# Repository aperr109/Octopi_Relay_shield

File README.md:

# Octopi_Relay_shield
simple relay shield for controlling a 3D printers power supply via a relay, using an octoprint configured RaspPi device

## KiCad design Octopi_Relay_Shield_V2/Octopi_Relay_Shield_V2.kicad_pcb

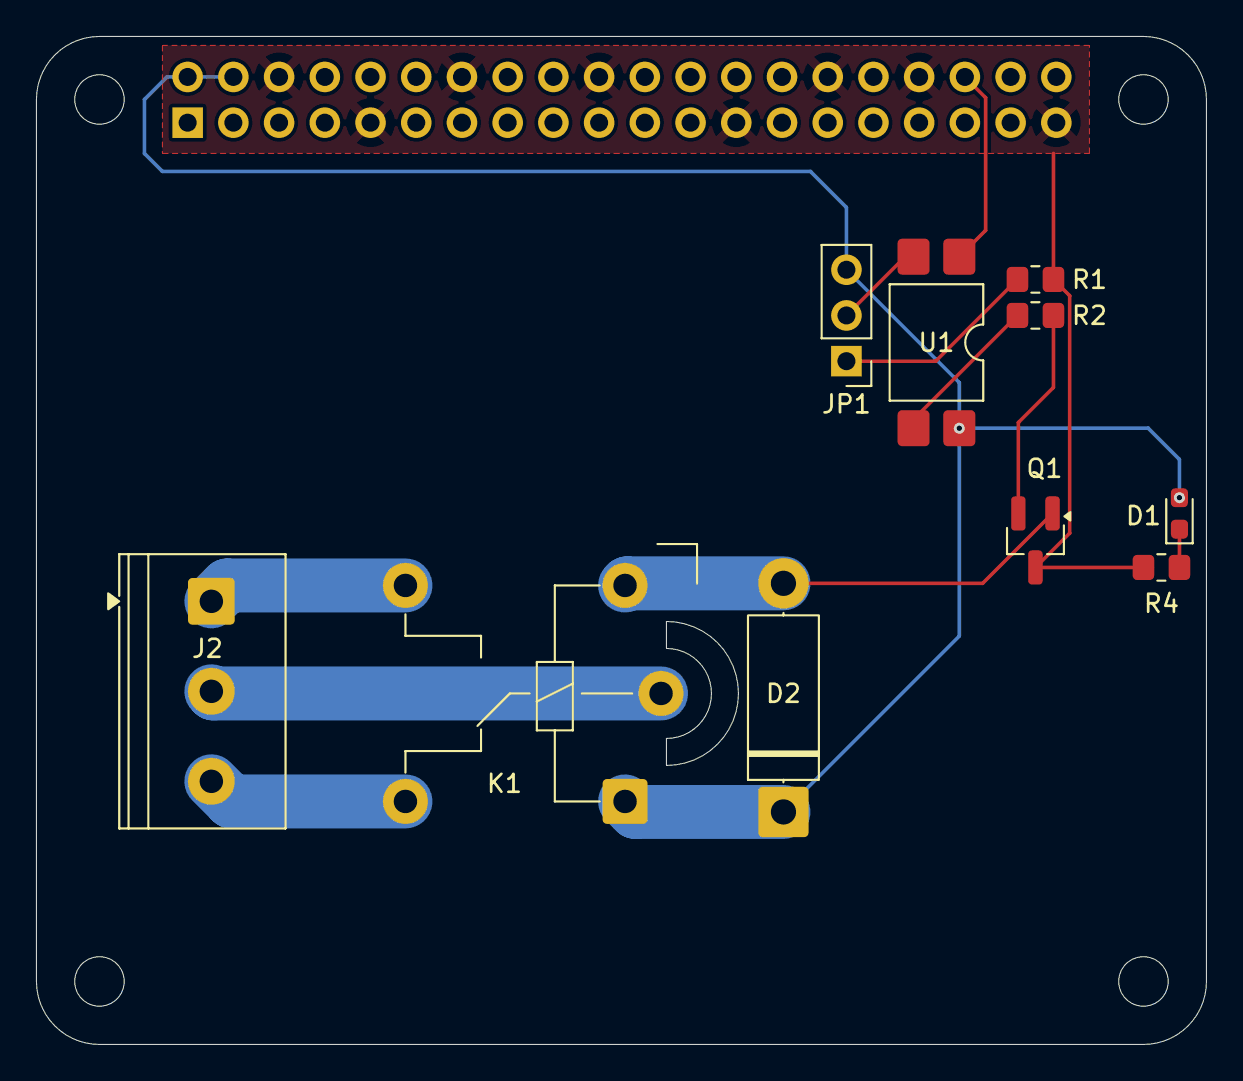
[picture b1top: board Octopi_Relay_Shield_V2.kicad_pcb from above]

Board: 2 copper layers, 65.0 x 56.0 mm, 11 parts (1 on the bottom side), 12 nets.

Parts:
D1: LED; LED_0603_1608Metric_Pad1.05x0.95mm_HandSolder
D2: D; D_5W_P12.70mm_Horizontal
J1: Raspberry_Pi_2_3; PinSocket_2x20_P2.54mm_Vertical
J2: Screw_Terminal_01x03; TerminalBlock_Phoenix_PT-1,5-3-5.0-H_1x03_P5.00mm_Horizontal
JP1: Jumper_3_Bridged12; PinHeader_1x03_P2.54mm_Vertical
K1: JQC-3FF-005-1Z; Relay_SPDT_Hongfa_JQC-3FF_0XX-1Z
Q1: NPN; SOT-23_Handsoldering
R1, R2, R4: R_1K; R_0805_2012Metric_Pad1.20x1.40mm_HandSolder
U1: LTV-817S; SMDIP-4_W9.53mm

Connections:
COM: J2.2, K1.11
GND1: J1.6 (GND), J1.9 (GND), J1.14 (GND), J1.20 (GND), J1.25 (GND), J1.30 (GND), J1.34 (GND), J1.39 (GND), Q1.3 (E), R1.1, R4.2
IN: J1.36 (GPIO16), U1.1
NC: J2.3, K1.12
NO: J2.1, K1.14
unnamed: D1.1 (K), R4.1
unnamed: D2.2 (A), K1.A2, Q1.1 (C)
unnamed: JP1.1 (A), R1.2
unnamed: JP1.2 (C), U1.2
unnamed: Q1.2 (B), R2.2
unnamed: R2.1, U1.3
VCC_5V: D1.2 (A), D2.1 (K), J1.2 (5V), J1.4 (5V), JP1.3 (B), K1.A1, U1.4

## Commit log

2025-10-23 made base schematics for two versions, slightly diff transistor configuration for each
2025-11-02 Completed Layout for first two designs, generated the fab files
    updated the nets, GND1 and GND2 have been joined into just GND1. separated GNDs would only be possible if there was a separate non-pi voltage source for the 5V on the other side of the octocoupler
